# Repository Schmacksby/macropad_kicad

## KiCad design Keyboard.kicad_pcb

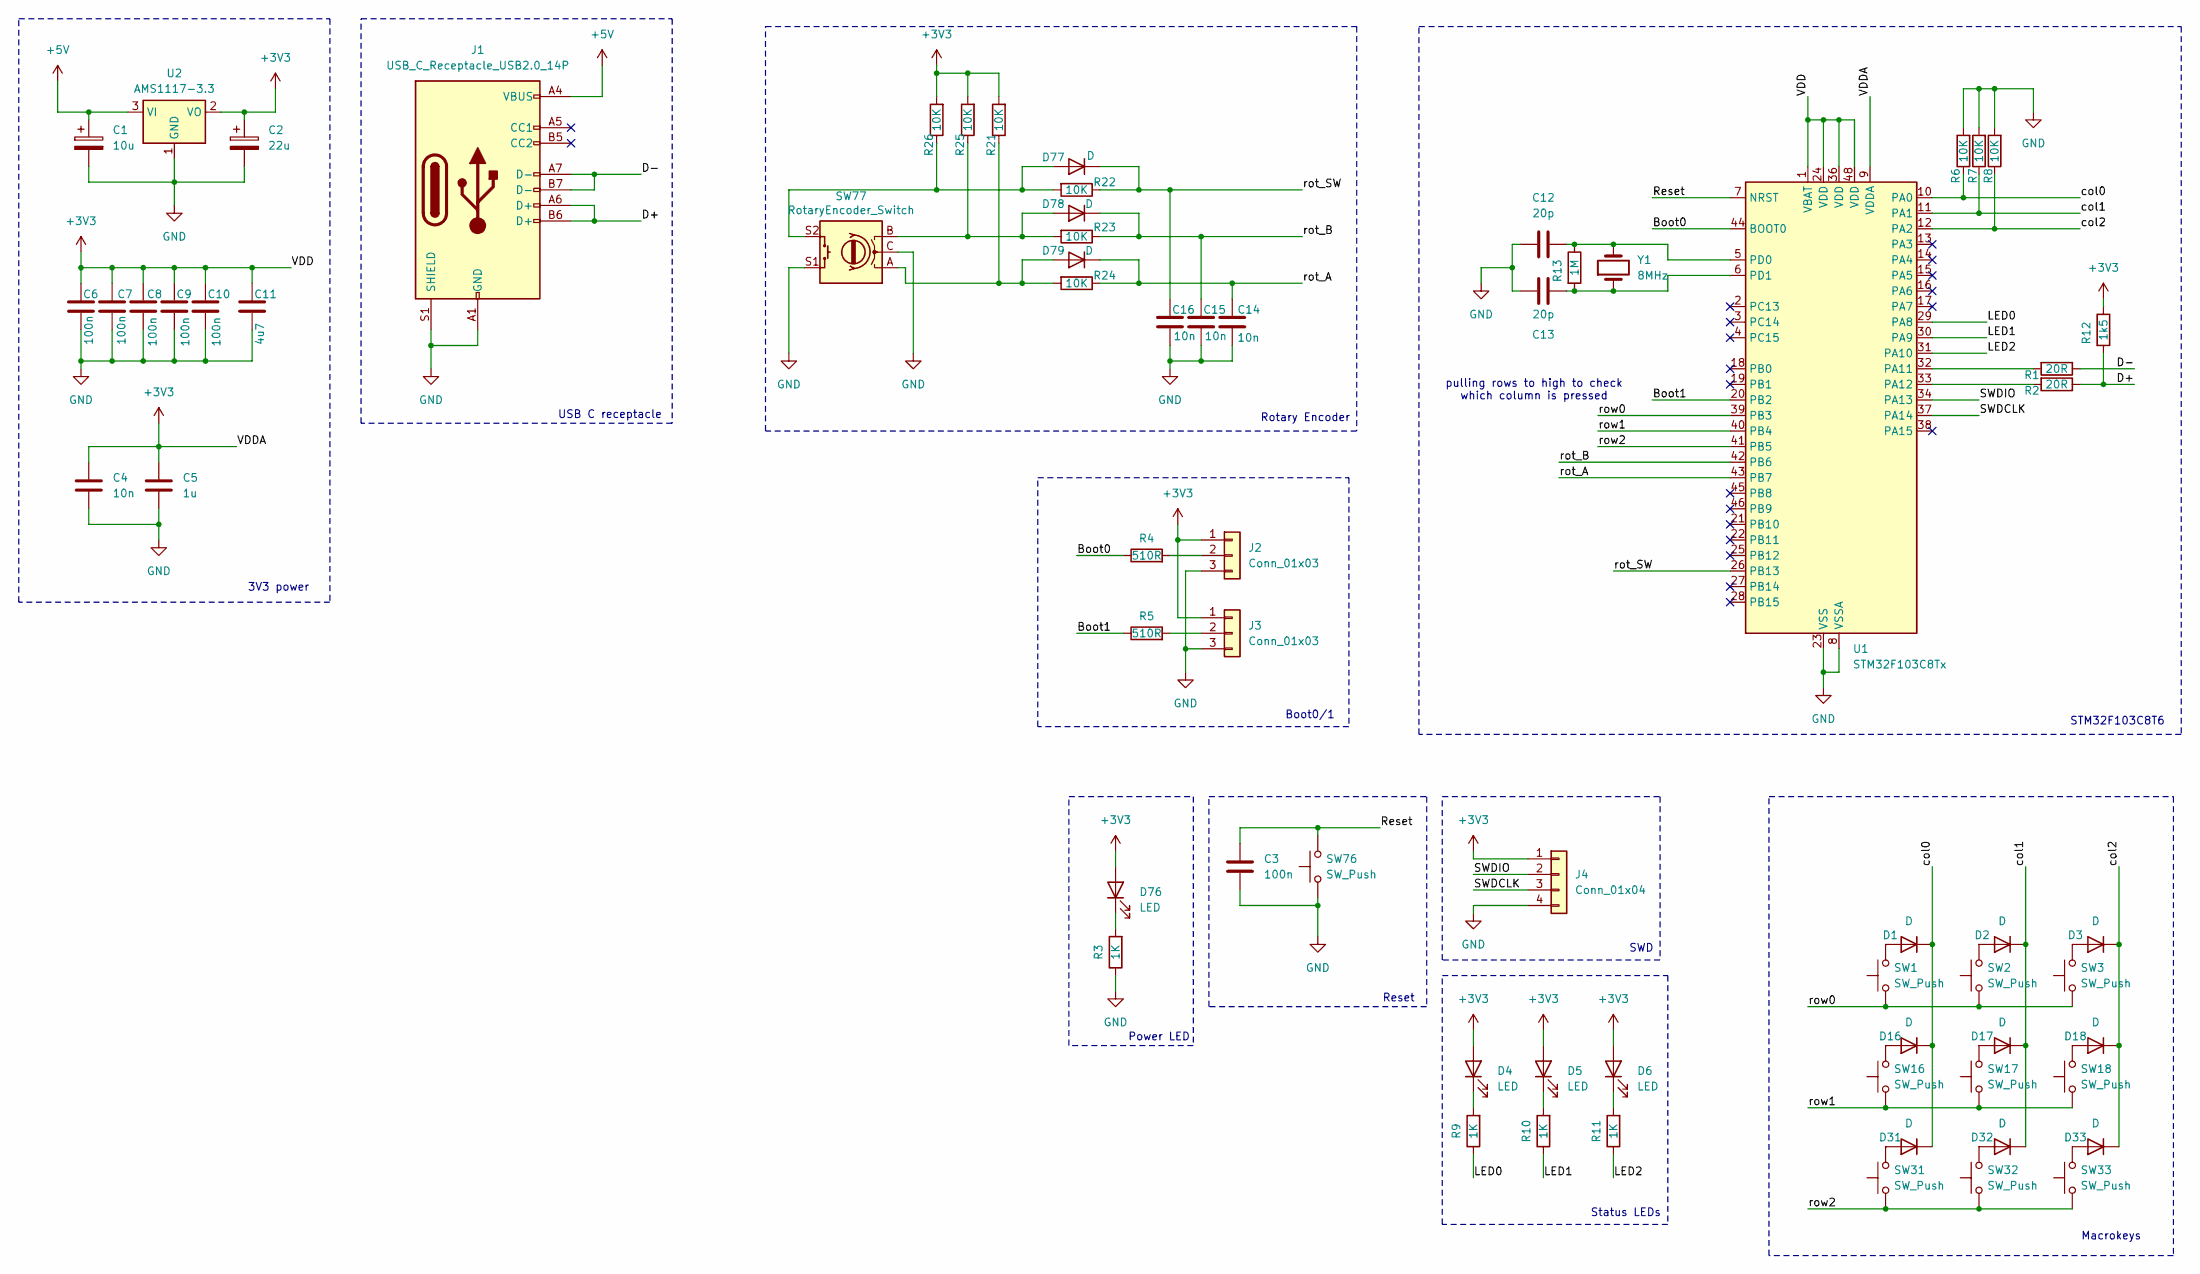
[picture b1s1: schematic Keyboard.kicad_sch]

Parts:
C1: 10u; C_0805_2012Metric_Pad1.18x1.45mm_HandSolder
C2: 22u; C_0805_2012Metric_Pad1.18x1.45mm_HandSolder
C3, C6, C7, C8, C9, C10: 100n; R_0603_1608Metric_Pad0.98x0.95mm_HandSolder
C4, C14, C15, C16: 10n; R_0603_1608Metric_Pad0.98x0.95mm_HandSolder
C5: 1u; R_0603_1608Metric_Pad0.98x0.95mm_HandSolder
C11: 4u7; R_0603_1608Metric_Pad0.98x0.95mm_HandSolder
C12, C13: 20p; R_0603_1608Metric_Pad0.98x0.95mm_HandSolder
D1, D2, D3, D16, D17, D18, D31, D32, D33, D77, D78, D79: D; D_SOD-523
D4, D5, D6, D76: LED; LED_D5.0mm
J1: USB_C_Receptacle_USB2.0_14P; USB_C_Receptacle_GCT_USB4105-xx-A_16P_TopMnt_Horizontal
J2, J3: Conn_01x03; PinHeader_1x03_P2.54mm_Horizontal
J4: Conn_01x04; PinHeader_1x04_P2.54mm_Horizontal
R1, R2: 20R; R_0603_1608Metric
R3, R9, R10, R11: 1K; R_0603_1608Metric
R4, R5: 510R; R_0603_1608Metric_Pad0.98x0.95mm_HandSolder
R6, R7, R8, R21, R22, R23, R24, R25, R26: 10K; R_0603_1608Metric
R12: 1k5; R_0603_1608Metric
R13: 1M; R_0603_1608Metric
SW1, SW2, SW3, SW16, SW17, SW18, SW31, SW32, SW33: SW_Push; Kailh_socket_MX
SW76: SW_Push; SW_Push_1P1T_NO_CK_KSC7xxJ
SW77: RotaryEncoder_Switch; RotaryEncoder_Alps_EC11E-Switch_Vertical_H20mm
U1: STM32F103C8Tx; LQFP-48_7x7mm_P0.5mm
U2: AMS1117-3.3; SOT-223-3_TabPin2
Y1: 8MHz; Crystal_HC49-U_Vertical

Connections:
+3V3: C2.1, C4.1, C5.1, C6.1, C7.1, C8.1, C9.1, C10.1, C11.1, D4.2 (A), D5.2 (A), D6.2 (A), D76.2 (A), J2.1, J3.1, J4.1, R12.1, R21.2, R25.2, R26.2, U1.1 (VBAT), U1.9 (VDDA), U1.24 (VDD), U1.36 (VDD), U1.48 (VDD), U2.2 (VO)
+5V: C1.1, J1.A4 (VBUS), J1.A9 (VBUS), J1.B4 (VBUS), J1.B9 (VBUS), U2.3 (VI)
/Boot0: R4.1, U1.44 (BOOT0)
/Boot1: R5.1, U1.20 (PB2)
/D+: J1.A6 (D+), J1.B6 (D+), R2.1, R12.2
/D-: J1.A7 (D-), J1.B7 (D-), R1.1
/LED0: R9.1, U1.29 (PA8)
/LED1: R10.1, U1.30 (PA9)
/LED2: R11.1, U1.31 (PA10)
/Reset: C3.1, SW76.2, U1.7 (NRST)
/SWDCLK: J4.3, U1.37 (PA14)
/SWDIO: J4.2, U1.34 (PA13)
/col0: D1.1 (K), D16.1 (K), D31.1 (K), R6.1, U1.10 (PA0)
/col1: D2.1 (K), D17.1 (K), D32.1 (K), R7.1, U1.11 (PA1)
/col2: D3.1 (K), D18.1 (K), D33.1 (K), R8.1, U1.12 (PA2)
/rot_A: C14.1, D79.1 (K), R24.1, U1.43 (PB7)
/rot_B: C15.1, D78.1 (K), R23.1, U1.42 (PB6)
/rot_SW: C16.1, D77.1 (K), R22.1, U1.26 (PB13)
/row0: SW1.1, SW2.1, SW3.1, U1.39 (PB3)
/row1: SW16.1, SW17.1, SW18.1, U1.40 (PB4)
/row2: SW31.1, SW32.1, SW33.1, U1.41 (PB5)
GND: C1.2, C2.2, C3.2, C4.2, C5.2, C6.2, C7.2, C8.2, C9.2, C10.2, C11.2, C12.1, C13.2, C14.2, C15.2, C16.2, J1.A1 (GND), J1.A12 (GND), J1.B1 (GND), J1.B12 (GND), J1.S1 (SHIELD), J2.3, J3.3, J4.4, R3.1, R6.2, R7.2, R8.2, SW76.1, SW77.C, SW77.S1, U1.8 (VSSA), U1.23 (VSS), U1.35 (VSS), U1.47 (VSS), U2.1 (GND)
unnamed: D1.2 (A), SW1.2
unnamed: D2.2 (A), SW2.2
unnamed: D3.2 (A), SW3.2
unnamed: D4.1 (K), R9.2
unnamed: D5.1 (K), R10.2
unnamed: D6.1 (K), R11.2
unnamed: D16.2 (A), SW16.2
unnamed: D17.2 (A), SW17.2
unnamed: D18.2 (A), SW18.2
unnamed: D31.2 (A), SW31.2
unnamed: D32.2 (A), SW32.2
unnamed: D33.2 (A), SW33.2
unnamed: D76.1 (K), R3.2
unnamed: D77.2 (A), R22.2, R26.1, SW77.S2
unnamed: D78.2 (A), R23.2, R25.1, SW77.B
unnamed: D79.2 (A), R21.1, R24.2, SW77.A
unnamed: J2.2, R4.2
unnamed: J3.2, R5.2
unnamed: R1.2, U1.32 (PA11)
unnamed: R2.2, U1.33 (PA12)
unnamed: C12.2, R13.1, U1.5 (PD0), Y1.2
unnamed: C13.1, R13.2, U1.6 (PD1), Y1.1

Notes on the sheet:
USB C receptacle
pulling rows to high to check which column is pressed
Power LED
Reset
3V3 power
STM32F103C8T6
Boot0/1
SWD
Macrokeys
Rotary Encoder
Status LEDs

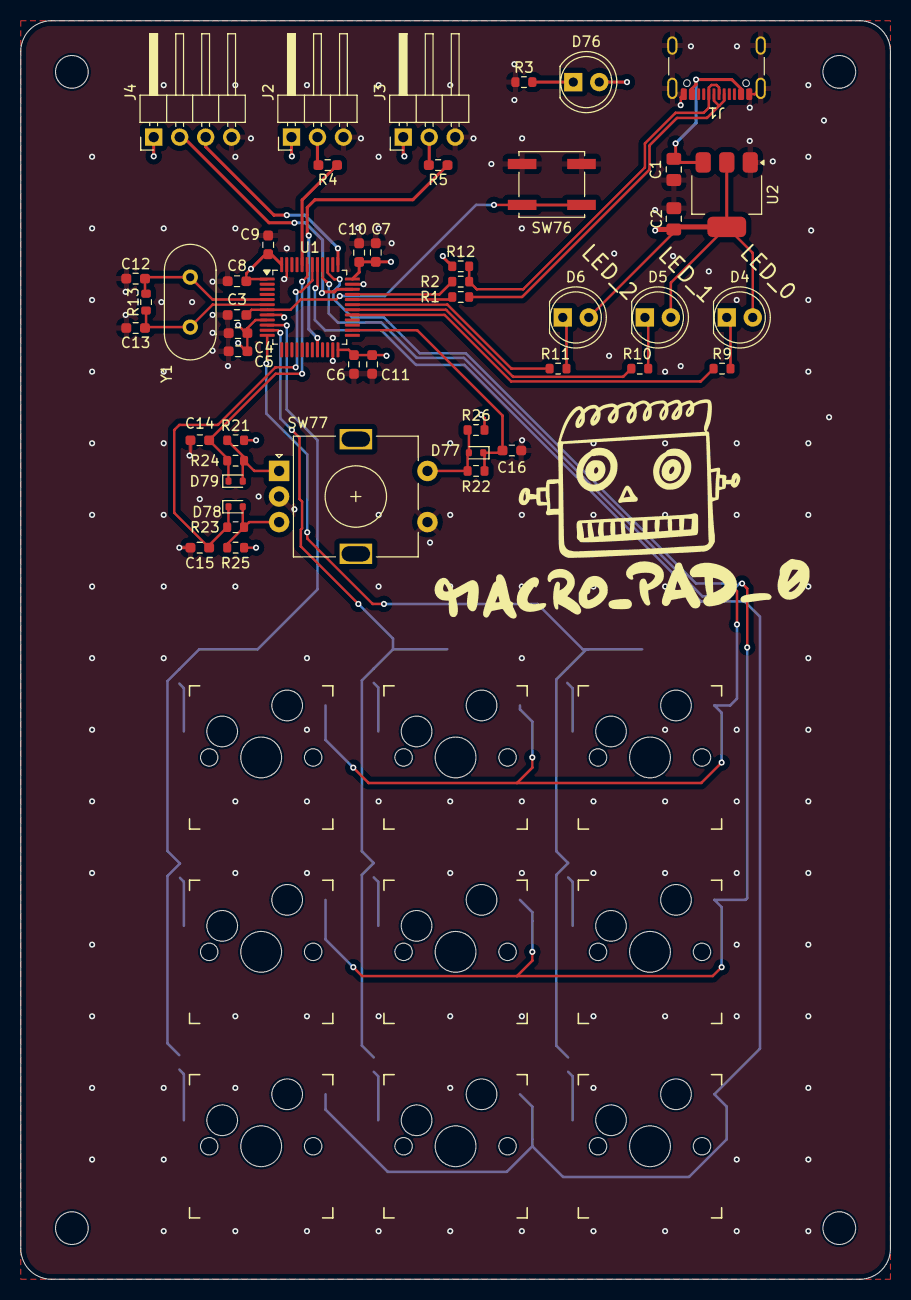
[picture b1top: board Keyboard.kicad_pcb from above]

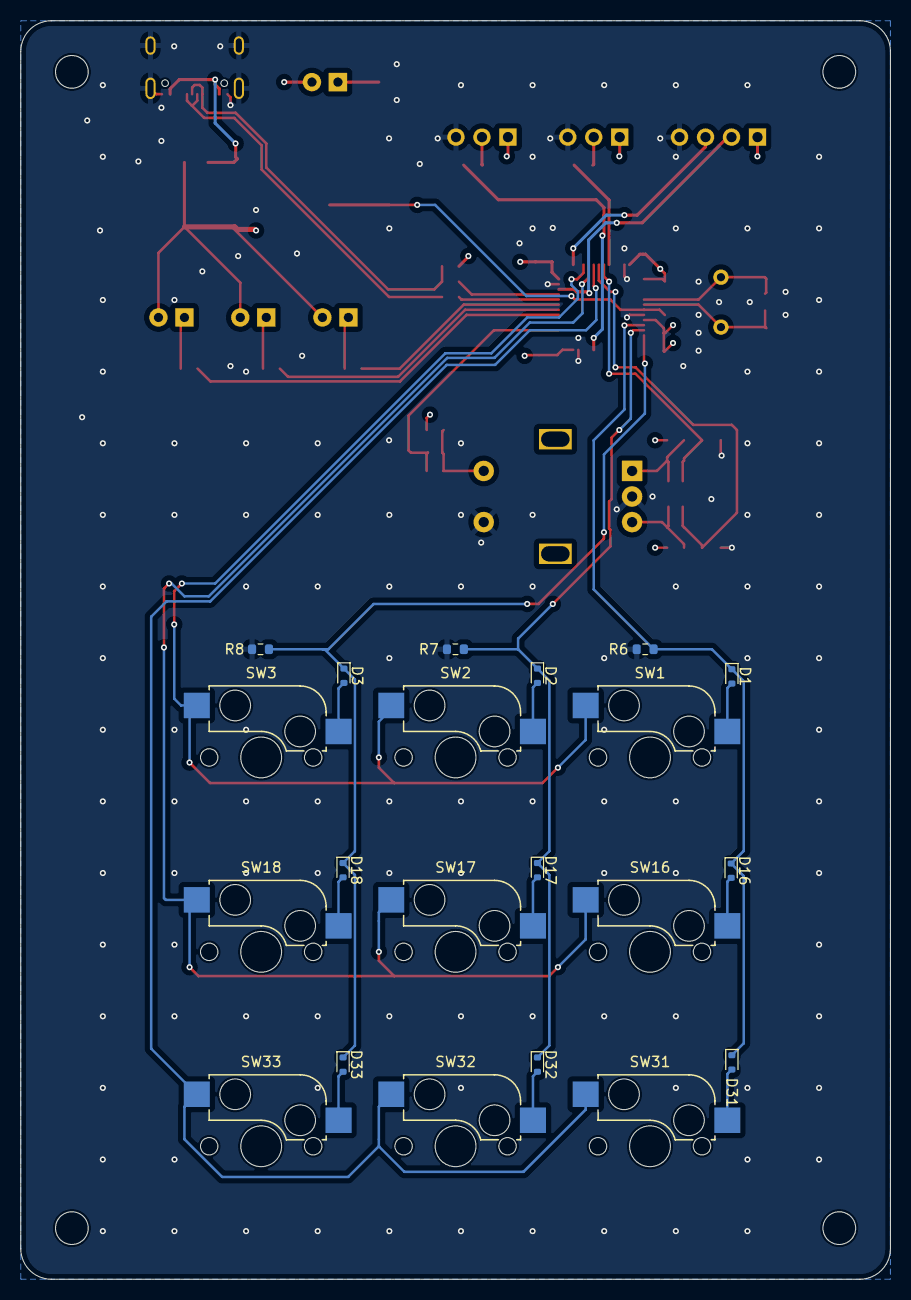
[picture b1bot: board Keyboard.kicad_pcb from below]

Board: 4 copper layers, 85.0 x 123.0 mm, 69 parts (12 on the bottom side), 44 nets.
